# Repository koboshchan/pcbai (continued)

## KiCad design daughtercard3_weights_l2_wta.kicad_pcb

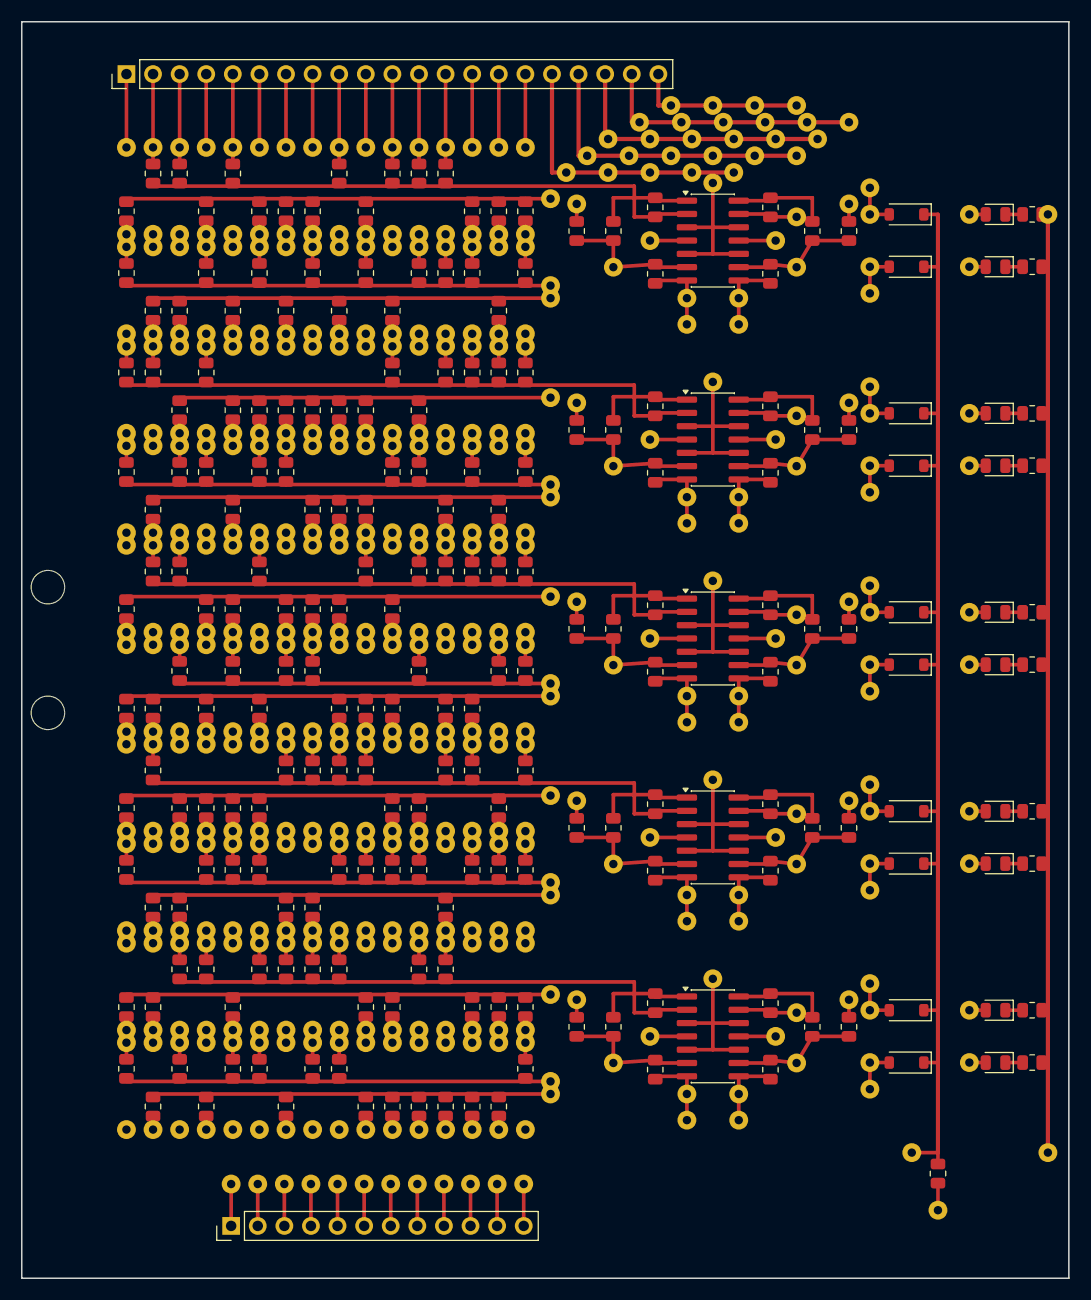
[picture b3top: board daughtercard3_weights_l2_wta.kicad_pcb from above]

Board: 2 copper layers, 100.0 x 120.0 mm, 474 parts (0 on the bottom side), 72 nets.

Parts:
D_0, D_1, D_2, D_3, D_4, D_5, D_6, D_7, D_8, D_9: 1N4148; D_SOD-123
J_BOT: SCORES_AND_WTA; PinHeader_1x12_P2.54mm_Vertical
J_TOP: ACT_IN_AND_PWR; PinHeader_1x21_P2.54mm_Vertical
LED_0, LED_1, LED_2, LED_3, LED_4, LED_5, LED_6, LED_7, LED_8, LED_9: RED; LED_0805_2012Metric
MH1, MH2: MountingHole_3.2mm_M3
R2_0_0, R2_0_6, R2_2_1, R2_3_2, R2_3_6, R2_4_6, R2_5_5, R2_6_4, R2_6_5, R2_7_1, R2_7_2, R2_7_5, R2_8_1, R2_10_1, R2_12_6, R2_12_9: 12k; R_0805_2012Metric
R2_0_1, R2_3_0, R2_3_9, R2_4_8, R2_5_1, R2_8_2, R2_9_2, R2_9_9: 18k; R_0805_2012Metric
R2_0_2, R2_0_4, R2_2_0, R2_2_7, R2_4_3, R2_5_9, R2_6_1, R2_6_9, R2_7_3, R2_8_9, R2_9_3, R2_10_9, R2_12_3, R2_14_1, R2_14_4, R2_14_6, R2_14_7: 22k; R_0805_2012Metric
R2_0_3, R2_0_7, R2_0_8, R2_1_5, R2_2_2, R2_4_4, R2_7_4, R2_8_5, R2_9_0, R2_9_6, R2_9_7, R2_10_2, R2_10_3, R2_10_7, R2_13_4: 33k; R_0805_2012Metric
R2_0_5, R2_4_5, R2_9_1, R2_14_8: 10k; R_0805_2012Metric
R2_0_9, R2_1_0, R2_1_6, R2_1_8, R2_5_3, R2_6_2, R2_8_6, R2_8_7, R2_9_5, R2_10_5, R2_10_8, R2_11_2, R2_11_7, R2_11_9, R2_13_5, R2_13_6, R2_13_7, R2_15_3, R2_15_7, R2_15_8: 75k; R_0805_2012Metric
R2_1_1, R2_1_3, R2_1_9, R2_2_3, R2_2_5, R2_3_8, R2_4_1, R2_4_2, R2_6_6, R2_7_6, R2_7_7, R2_11_4, R2_12_4, R2_14_5, R2_15_4: 51k; R_0805_2012Metric
R2_1_2, R2_1_7, R2_11_1, R2_12_1, R2_12_8, R2_15_2, R2_15_9: 300k; R_0805_2012Metric
R2_1_4, R2_2_8, R2_4_9, R2_6_8, R2_7_8, R2_7_9, R2_8_0, R2_10_6, R2_11_0, R2_11_5, R2_11_6, R2_11_8, R2_13_1, R2_13_8, R2_15_0, R2_15_6: 100k; R_0805_2012Metric
R2_2_4, R2_12_2: 47k; R_0805_2012Metric
R2_2_6, R2_3_4, R2_4_7, R2_6_3, R2_6_7, R2_8_8, R2_9_4, R2_10_0, R2_14_2: 15k; R_0805_2012Metric
R2_2_9, R2_3_3, R2_3_5, R2_5_2, R2_7_0, R2_9_8, R2_13_2: 43k; R_0805_2012Metric
R2_3_1, R2_3_7: 390k; R_0805_2012Metric
R2_4_0, R2_5_7, R2_8_4, R2_11_3, R2_12_5, R2_13_3, R2_13_9, R2_14_0, R2_14_3, R2_14_9, R2_15_1: 200k; R_0805_2012Metric
R2_5_0, R2_5_6, R2_10_4: 7.5k; R_0805_2012Metric
R2_5_4, R2_6_0, R2_8_3: 20k; R_0805_2012Metric
R2_5_8: 470k; R_0805_2012Metric
R2_12_0, R2_15_5: 1M; R_0805_2012Metric
R2_12_7: 5.6k; R_0805_2012Metric
R2_13_0: 680k; R_0805_2012Metric
R_LED0, R_LED1, R_LED2, R_LED3, R_LED4, R_LED5, R_LED6, R_LED7, R_LED8, R_LED9: 1k; R_0805_2012Metric
R_WTA: 10k; R_0805_2012Metric
Rb_L2_0: 390k; R_0805_2012Metric
Rb_L2_1: 47k; R_0805_2012Metric
Rb_L2_2, Rb_L2_8: 200k; R_0805_2012Metric
Rb_L2_3, Rb_L2_4, Rb_L2_6, Rb_L2_7, Rb_L2_9: 100k; R_0805_2012Metric
Rb_L2_5: 1M; R_0805_2012Metric
Rc_L2_0, Rc_L2_1, Rc_L2_2, Rc_L2_3, Rc_L2_4, Rc_L2_5, Rc_L2_6, Rc_L2_7, Rc_L2_8, Rc_L2_9: 10k; R_0805_2012Metric
Rf1_L2_0, Rf1_L2_1, Rf1_L2_2, Rf1_L2_3, Rf1_L2_4, Rf1_L2_5, Rf1_L2_6, Rf1_L2_7, Rf1_L2_8, Rf1_L2_9: 10k; R_0805_2012Metric
Rf_L2_0, Rf_L2_1, Rf_L2_2, Rf_L2_3, Rf_L2_4, Rf_L2_5, Rf_L2_6, Rf_L2_7, Rf_L2_8, Rf_L2_9: 10k; R_0805_2012Metric
U1, U2, U3, U4, U5: TL074; SOIC-14_3.9x8.7mm_P1.27mm
W1, W2, W3, W4, W5, W6, W7, W8, W9, W10, W11, W12, W13, W14, W15, W16, W17, W18, W19, W20, W21, W22, W23, W24, W25, W26, W27, W28, W29, W30, W31, W32, W33, W34, W35, W36, W37, W38, W39, W40, W41, W42, W43, W44, W45, W46, W47, W48, W49, W50, W51, W52, W53, W54, W55, W56, W57, W58, W59, W60, W61, W62, W63, W64, W65, W66, W67, W68, W69, W70, W71, W72, W73, W74, W75, W76, W77, W78, W79, W80, W81, W82, W83, W84, W85, W86, W87, W88, W89, W90, W91, W92, W93, W94, W95, W96, W97, W98, W99, W100, W101, W102, W103, W104, W105, W106, W107, W108, W109, W110, W111, W112, W113, W114, W115, W116, W117, W118, W119, W120, W121, W122, W123, W124, W125, W126, W127, W128, W129, W130, W131, W132, W133, W134, W135, W136, W137, W138, W139, W140, W141, W142, W143, W144, W145, W146, W147, W148, W149, W150, W151, W152, W153, W154, W155, W156, W157, W158, W159, W160, W161, W162, W163, W164, W165, W166, W167, W168, W169, W170, W171, W172, W173, W174, W175, W176, W177, W178, W179, W180, W181, W182, W183, W184, W185, W186, W187, W188, W189, W190, W191, W192, W193, W194, W195, W196, W197, W198, W199, W200, W201, W202, W203, W204, W205, W206, W207, W208, W209, W210, W211, W212, W213, W214, W215, W216, W217, W218, W219, W220, W221, W222, W223, W224, W225, W226, W227, W228, W229, W230, W231, W232, W233, W234: JUMPER; Jumper_Wire

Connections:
+5V_REF: J_TOP.20, Rb_L2_0.1, Rb_L2_2.1, Rb_L2_3.1, Rb_L2_5.1, Rb_L2_8.1, Rb_L2_9.1, W169.1, W183.1, W186.1, W200.1, W225.1, W228.1
+12V: J_TOP.17, U1.4, U2.4, U3.4, U4.4, U5.4, W166.1, W180.1, W194.1, W208.1, W222.1
-5V_REF: J_TOP.21, Rb_L2_1.1, Rb_L2_4.1, Rb_L2_6.1, Rb_L2_7.1, W172.1, W197.1, W211.1, W214.1
-12V: J_TOP.18, R_WTA.2, U1.11, U2.11, U3.11, U4.11, U5.11, W162.1, W167.1, W181.1, W195.1, W209.1, W223.1
ACT_0: J_TOP.1, R2_0_0.1, R2_0_1.1, R2_0_2.1, R2_0_3.1, R2_0_4.1, R2_0_5.1, R2_0_6.1, R2_0_7.1, R2_0_8.1, R2_0_9.1, W1.1, W2.1, W3.1, W4.1, W5.1, W6.1, W7.1, W8.1, W9.1, W10.1
ACT_1: J_TOP.2, R2_1_0.1, R2_1_1.1, R2_1_2.1, R2_1_3.1, R2_1_4.1, R2_1_5.1, R2_1_6.1, R2_1_7.1, R2_1_8.1, R2_1_9.1, W11.1, W12.1, W13.1, W14.1, W15.1, W16.1, W17.1, W18.1, W19.1, W20.1
ACT_2: J_TOP.3, R2_2_0.1, R2_2_1.1, R2_2_2.1, R2_2_3.1, R2_2_4.1, R2_2_5.1, R2_2_6.1, R2_2_7.1, R2_2_8.1, R2_2_9.1, W21.1, W22.1, W23.1, W24.1, W25.1, W26.1, W27.1, W28.1, W29.1, W30.1
ACT_3: J_TOP.4, R2_3_0.1, R2_3_1.1, R2_3_2.1, R2_3_3.1, R2_3_4.1, R2_3_5.1, R2_3_6.1, R2_3_7.1, R2_3_8.1, R2_3_9.1, W31.1, W32.1, W33.1, W34.1, W35.1, W36.1, W37.1, W38.1, W39.1, W40.1
ACT_4: J_TOP.5, R2_4_0.1, R2_4_1.1, R2_4_2.1, R2_4_3.1, R2_4_4.1, R2_4_5.1, R2_4_6.1, R2_4_7.1, R2_4_8.1, R2_4_9.1, W41.1, W42.1, W43.1, W44.1, W45.1, W46.1, W47.1, W48.1, W49.1, W50.1
ACT_5: J_TOP.6, R2_5_0.1, R2_5_1.1, R2_5_2.1, R2_5_3.1, R2_5_4.1, R2_5_5.1, R2_5_6.1, R2_5_7.1, R2_5_8.1, R2_5_9.1, W51.1, W52.1, W53.1, W54.1, W55.1, W56.1, W57.1, W58.1, W59.1, W60.1
ACT_6: J_TOP.7, R2_6_0.1, R2_6_1.1, R2_6_2.1, R2_6_3.1, R2_6_4.1, R2_6_5.1, R2_6_6.1, R2_6_7.1, R2_6_8.1, R2_6_9.1, W61.1, W62.1, W63.1, W64.1, W65.1, W66.1, W67.1, W68.1, W69.1, W70.1
ACT_7: J_TOP.8, R2_7_0.1, R2_7_1.1, R2_7_2.1, R2_7_3.1, R2_7_4.1, R2_7_5.1, R2_7_6.1, R2_7_7.1, R2_7_8.1, R2_7_9.1, W71.1, W72.1, W73.1, W74.1, W75.1, W76.1, W77.1, W78.1, W79.1, W80.1
ACT_8: J_TOP.9, R2_8_0.1, R2_8_1.1, R2_8_2.1, R2_8_3.1, R2_8_4.1, R2_8_5.1, R2_8_6.1, R2_8_7.1, R2_8_8.1, R2_8_9.1, W81.1, W82.1, W83.1, W84.1, W85.1, W86.1, W87.1, W88.1, W89.1, W90.1
ACT_9: J_TOP.10, R2_9_0.1, R2_9_1.1, R2_9_2.1, R2_9_3.1, R2_9_4.1, R2_9_5.1, R2_9_6.1, R2_9_7.1, R2_9_8.1, R2_9_9.1, W91.1, W92.1, W93.1, W94.1, W95.1, W96.1, W97.1, W98.1, W99.1, W100.1
ACT_10: J_TOP.11, R2_10_0.1, R2_10_1.1, R2_10_2.1, R2_10_3.1, R2_10_4.1, R2_10_5.1, R2_10_6.1, R2_10_7.1, R2_10_8.1, R2_10_9.1, W101.1, W102.1, W103.1, W104.1, W105.1, W106.1, W107.1, W108.1, W109.1, W110.1
ACT_11: J_TOP.12, R2_11_0.1, R2_11_1.1, R2_11_2.1, R2_11_3.1, R2_11_4.1, R2_11_5.1, R2_11_6.1, R2_11_7.1, R2_11_8.1, R2_11_9.1, W111.1, W112.1, W113.1, W114.1, W115.1, W116.1, W117.1, W118.1, W119.1, W120.1
ACT_12: J_TOP.13, R2_12_0.1, R2_12_1.1, R2_12_2.1, R2_12_3.1, R2_12_4.1, R2_12_5.1, R2_12_6.1, R2_12_7.1, R2_12_8.1, R2_12_9.1, W121.1, W122.1, W123.1, W124.1, W125.1, W126.1, W127.1, W128.1, W129.1, W130.1
ACT_13: J_TOP.14, R2_13_0.1, R2_13_1.1, R2_13_2.1, R2_13_3.1, R2_13_4.1, R2_13_5.1, R2_13_6.1, R2_13_7.1, R2_13_8.1, R2_13_9.1, W131.1, W132.1, W133.1, W134.1, W135.1, W136.1, W137.1, W138.1, W139.1, W140.1
ACT_14: J_TOP.15, R2_14_0.1, R2_14_1.1, R2_14_2.1, R2_14_3.1, R2_14_4.1, R2_14_5.1, R2_14_6.1, R2_14_7.1, R2_14_8.1, R2_14_9.1, W141.1, W142.1, W143.1, W144.1, W145.1, W146.1, W147.1, W148.1, W149.1, W150.1
ACT_15: J_TOP.16, R2_15_0.1, R2_15_1.1, R2_15_2.1, R2_15_3.1, R2_15_4.1, R2_15_5.1, R2_15_6.1, R2_15_7.1, R2_15_8.1, R2_15_9.1, W151.1, W152.1, W153.1, W154.1, W155.1, W156.1, W157.1, W158.1, W159.1, W160.1
GND: J_BOT.12, J_TOP.19, R_LED0.2, R_LED1.2, R_LED2.2, R_LED3.2, R_LED4.2, R_LED5.2, R_LED6.2, R_LED7.2, R_LED8.2, R_LED9.2, U1.3, U1.5, U1.10, U1.12, U2.3, U2.5, U2.10, U2.12, U3.3, U3.5, U3.10, U3.12, U4.3, U4.5, U4.10, U4.12, U5.3, U5.5, U5.10, U5.12, W163.1, W164.1, W165.1, W179.1, W193.1, W207.1, W221.1
LED_NET_0: LED_0.1, R_LED0.1
LED_NET_1: LED_1.1, R_LED1.1
LED_NET_2: LED_2.1, R_LED2.1
LED_NET_3: LED_3.1, R_LED3.1
LED_NET_4: LED_4.1, R_LED4.1
LED_NET_5: LED_5.1, R_LED5.1
LED_NET_6: LED_6.1, R_LED6.1
LED_NET_7: LED_7.1, R_LED7.1
LED_NET_8: LED_8.1, R_LED8.1
LED_NET_9: LED_9.1, R_LED9.1
SUM_L2_NEG_0: R2_0_0.2, R2_3_0.2, R2_5_0.2, R2_6_0.2, R2_7_0.2, R2_9_0.2, R2_13_0.2, R2_14_0.2, R2_15_0.2, Rb_L2_0.2, Rc_L2_0.2, Rf_L2_0.1, U1.6, W168.1
SUM_L2_NEG_1: R2_1_1.2, R2_2_1.2, R2_4_1.2, R2_6_1.2, R2_8_1.2, R2_10_1.2, R2_14_1.2, Rb_L2_1.2, Rc_L2_1.2, Rf_L2_1.1, U1.9, W171.1
SUM_L2_NEG_2: R2_2_2.2, R2_4_2.2, R2_5_2.2, R2_6_2.2, R2_7_2.2, R2_8_2.2, R2_9_2.2, R2_11_2.2, Rb_L2_2.2, Rc_L2_2.2, Rf_L2_2.1, U2.6, W182.1
SUM_L2_NEG_3: R2_1_3.2, R2_4_3.2, R2_7_3.2, R2_8_3.2, R2_9_3.2, R2_12_3.2, R2_14_3.2, Rb_L2_3.2, Rc_L2_3.2, Rf_L2_3.1, U2.9, W185.1
SUM_L2_NEG_4: R2_0_4.2, R2_3_4.2, R2_4_4.2, R2_6_4.2, R2_7_4.2, R2_8_4.2, R2_10_4.2, Rb_L2_4.2, Rc_L2_4.2, Rf_L2_4.1, U3.6, W196.1
SUM_L2_NEG_5: R2_0_5.2, R2_1_5.2, R2_3_5.2, R2_5_5.2, R2_8_5.2, R2_9_5.2, R2_10_5.2, R2_12_5.2, R2_13_5.2, Rb_L2_5.2, Rc_L2_5.2, Rf_L2_5.1, U3.9, W199.1
SUM_L2_NEG_6: R2_0_6.2, R2_2_6.2, R2_3_6.2, R2_4_6.2, R2_5_6.2, R2_10_6.2, R2_11_6.2, R2_14_6.2, Rb_L2_6.2, Rc_L2_6.2, Rf_L2_6.1, U4.6, W210.1
SUM_L2_NEG_7: R2_1_7.2, R2_2_7.2, R2_6_7.2, R2_7_7.2, R2_12_7.2, Rb_L2_7.2, Rc_L2_7.2, Rf_L2_7.1, U4.9, W213.1
SUM_L2_NEG_8: R2_0_8.2, R2_1_8.2, R2_4_8.2, R2_9_8.2, R2_10_8.2, R2_13_8.2, R2_14_8.2, R2_15_8.2, Rb_L2_8.2, Rc_L2_8.2, Rf_L2_8.1, U5.6, W224.1
SUM_L2_NEG_9: R2_1_9.2, R2_3_9.2, R2_6_9.2, R2_9_9.2, R2_10_9.2, R2_11_9.2, R2_12_9.2, R2_13_9.2, R2_14_9.2, Rb_L2_9.2, Rc_L2_9.2, Rf_L2_9.1, U5.9, W227.1
SUM_L2_POS_0: R2_1_0.2, R2_2_0.2, R2_4_0.2, R2_8_0.2, R2_10_0.2, R2_11_0.2, R2_12_0.2, Rf1_L2_0.2, U1.2
SUM_L2_POS_1: R2_0_1.2, R2_3_1.2, R2_5_1.2, R2_7_1.2, R2_9_1.2, R2_11_1.2, R2_12_1.2, R2_13_1.2, R2_15_1.2, Rf1_L2_1.2, U1.13, W170.1
SUM_L2_POS_2: R2_0_2.2, R2_1_2.2, R2_3_2.2, R2_10_2.2, R2_12_2.2, R2_13_2.2, R2_14_2.2, R2_15_2.2, Rf1_L2_2.2, U2.2
SUM_L2_POS_3: R2_0_3.2, R2_2_3.2, R2_3_3.2, R2_5_3.2, R2_6_3.2, R2_10_3.2, R2_11_3.2, R2_13_3.2, R2_15_3.2, Rf1_L2_3.2, U2.13, W184.1
SUM_L2_POS_4: R2_1_4.2, R2_2_4.2, R2_5_4.2, R2_9_4.2, R2_11_4.2, R2_12_4.2, R2_13_4.2, R2_14_4.2, R2_15_4.2, Rf1_L2_4.2, U3.2
SUM_L2_POS_5: R2_2_5.2, R2_4_5.2, R2_6_5.2, R2_7_5.2, R2_11_5.2, R2_14_5.2, R2_15_5.2, Rf1_L2_5.2, U3.13, W198.1
SUM_L2_POS_6: R2_1_6.2, R2_6_6.2, R2_7_6.2, R2_8_6.2, R2_9_6.2, R2_12_6.2, R2_13_6.2, R2_15_6.2, Rf1_L2_6.2, U4.2
SUM_L2_POS_7: R2_0_7.2, R2_3_7.2, R2_4_7.2, R2_5_7.2, R2_8_7.2, R2_9_7.2, R2_10_7.2, R2_11_7.2, R2_13_7.2, R2_14_7.2, R2_15_7.2, Rf1_L2_7.2, U4.13, W212.1
SUM_L2_POS_8: R2_2_8.2, R2_3_8.2, R2_5_8.2, R2_6_8.2, R2_7_8.2, R2_8_8.2, R2_11_8.2, R2_12_8.2, Rf1_L2_8.2, U5.2
SUM_L2_POS_9: R2_0_9.2, R2_2_9.2, R2_4_9.2, R2_5_9.2, R2_7_9.2, R2_8_9.2, R2_15_9.2, Rf1_L2_9.2, U5.13, W226.1
V_INV_0: Rc_L2_0.1, Rf1_L2_0.1, U1.1
V_INV_1: Rc_L2_1.1, Rf1_L2_1.1, U1.14
V_INV_2: Rc_L2_2.1, Rf1_L2_2.1, U2.1
V_INV_3: Rc_L2_3.1, Rf1_L2_3.1, U2.14
V_INV_4: Rc_L2_4.1, Rf1_L2_4.1, U3.1
V_INV_5: Rc_L2_5.1, Rf1_L2_5.1, U3.14
V_INV_6: Rc_L2_6.1, Rf1_L2_6.1, U4.1
V_INV_7: Rc_L2_7.1, Rf1_L2_7.1, U4.14
V_INV_8: Rc_L2_8.1, Rf1_L2_8.1, U5.1
V_INV_9: Rc_L2_9.1, Rf1_L2_9.1, U5.14
V_SUM_0: D_0.2, J_BOT.1, LED_0.2, Rf_L2_0.2, U1.7, W173.1, W174.1, W175.1
V_SUM_1: D_1.2, J_BOT.2, LED_1.2, Rf_L2_1.2, U1.8, W176.1, W177.1, W178.1
V_SUM_2: D_2.2, J_BOT.3, LED_2.2, Rf_L2_2.2, U2.7, W187.1, W188.1, W189.1
V_SUM_3: D_3.2, J_BOT.4, LED_3.2, Rf_L2_3.2, U2.8, W190.1, W191.1, W192.1
V_SUM_4: D_4.2, J_BOT.5, LED_4.2, Rf_L2_4.2, U3.7, W201.1, W202.1, W203.1
V_SUM_5: D_5.2, J_BOT.6, LED_5.2, Rf_L2_5.2, U3.8, W204.1, W205.1, W206.1
V_SUM_6: D_6.2, J_BOT.7, LED_6.2, Rf_L2_6.2, U4.7, W215.1, W216.1, W217.1
V_SUM_7: D_7.2, J_BOT.8, LED_7.2, Rf_L2_7.2, U4.8, W218.1, W219.1, W220.1
V_SUM_8: D_8.2, J_BOT.9, LED_8.2, Rf_L2_8.2, U5.7, W229.1, W230.1, W231.1
V_SUM_9: D_9.2, J_BOT.10, LED_9.2, Rf_L2_9.2, U5.8, W232.1, W233.1, W234.1
WTA_BUS: D_0.1, D_1.1, D_2.1, D_3.1, D_4.1, D_5.1, D_6.1, D_7.1, D_8.1, D_9.1, J_BOT.11, R_WTA.1, W161.1

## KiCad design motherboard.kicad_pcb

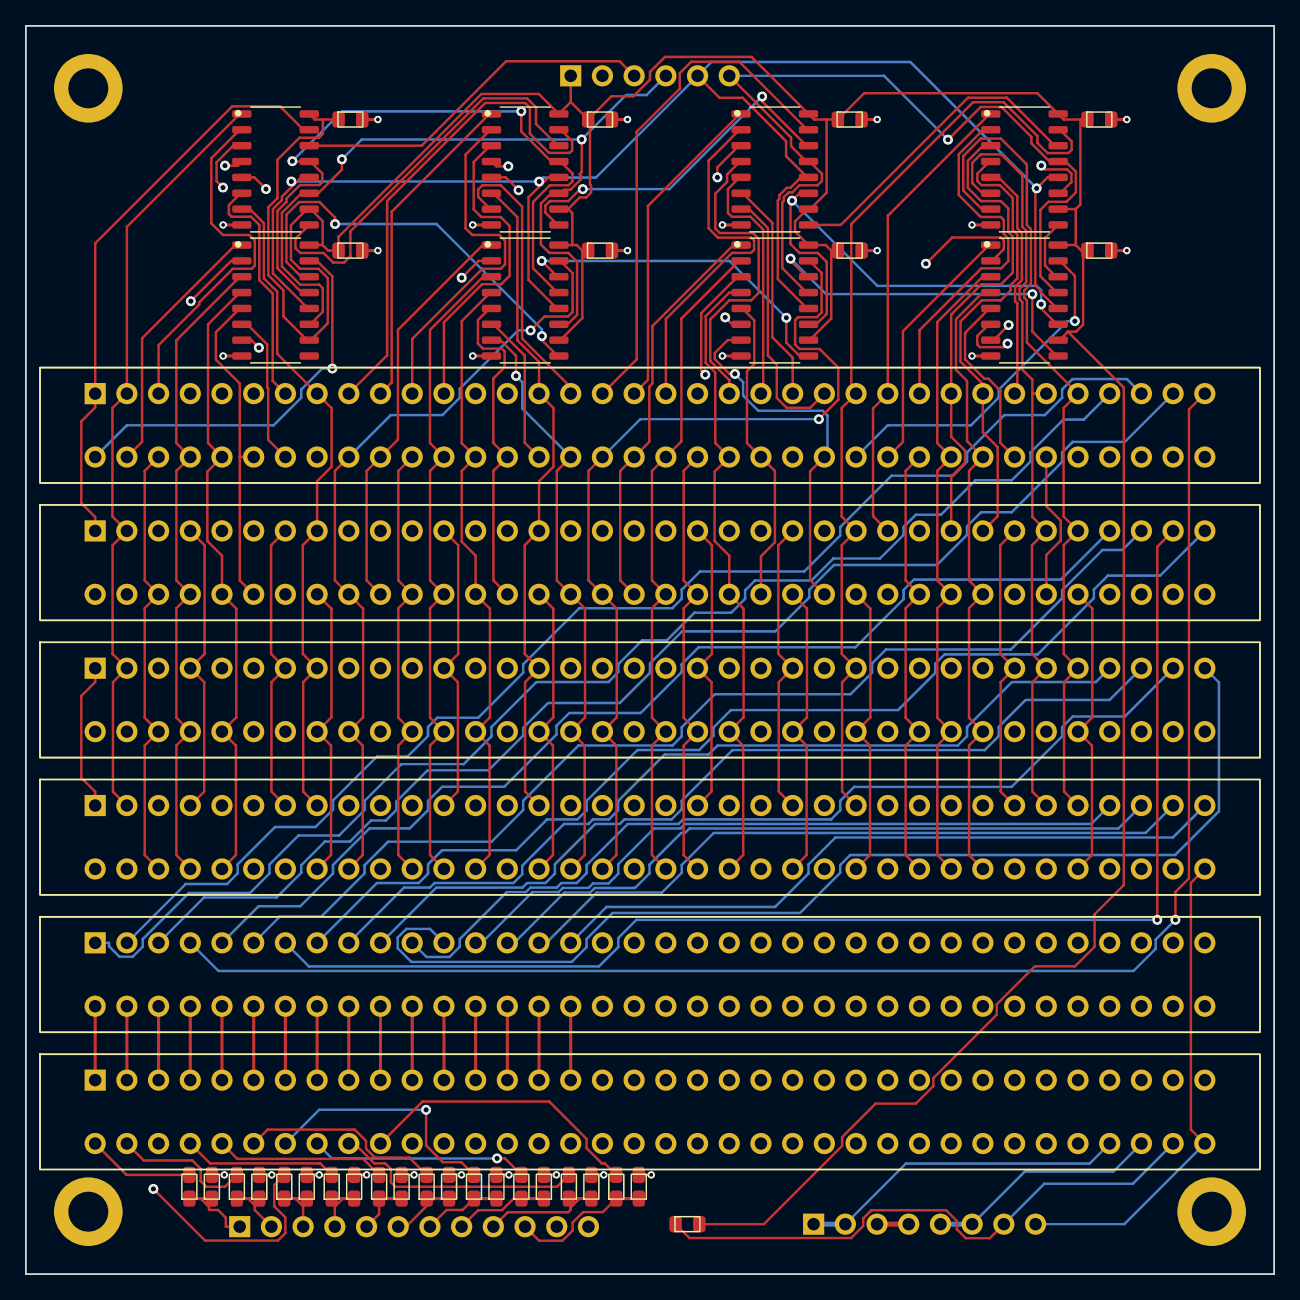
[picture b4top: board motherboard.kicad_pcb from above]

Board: 4 copper layers, 100.0 x 100.0 mm, 50 parts (0 on the bottom side), 133 nets.

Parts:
C_SR1, C_SR2, C_SR3, C_SR4, C_SR5, C_SR6, C_SR7, C_SR8: 0.1uF; C_0805_2012Metric
H1, H2, H3, H4: MountingHole; MountingHole_3.2mm_M3_Pad
J_MCU_SCORES: Scores_DIV_3V3_Out; PinHeader_1x12_P2.54mm_Vertical
J_MCU_SPI: MCU_SPI_In; PinHeader_1x06_P2.54mm_Vertical
J_PWR_IN: Main_Power_In; PinHeader_1x08_P2.54mm_Vertical
J_SLOT0: Slot0: DC1A (L1 Neurons 0..3); S-072M-2.54-5
J_SLOT1: Slot1: DC1B (L1 Neurons 4..7); S-072M-2.54-5
J_SLOT2: Slot2: DC1C (L1 Neurons 8..11); S-072M-2.54-5
J_SLOT3: Slot3: DC1D (L1 Neurons 12..15); S-072M-2.54-5
J_SLOT4: Slot4: DC2 (16x Active Precision ReLU); S-072M-2.54-5
J_SLOT5: Slot5: DC3 (L2 Weights + 10-Way WTA); S-072M-2.54-5
R_BOT_0, R_BOT_1, R_BOT_2, R_BOT_3, R_BOT_4, R_BOT_5, R_BOT_6, R_BOT_7, R_BOT_8, R_BOT_9: 20k; R_0805_2012Metric
R_PWR5: 0R; R_0805_2012Metric
R_TOP_0, R_TOP_1, R_TOP_2, R_TOP_3, R_TOP_4, R_TOP_5, R_TOP_6, R_TOP_7, R_TOP_8, R_TOP_9: 10k; R_0805_2012Metric
U_SR1, U_SR2, U_SR3, U_SR4, U_SR5, U_SR6, U_SR7, U_SR8: 74HC595D; SOIC-16_3.9x9.9mm_P1.27mm

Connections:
+5V: C_SR1.1, C_SR2.1, C_SR3.1, C_SR4.1, C_SR5.1, C_SR6.1, C_SR7.1, C_SR8.1, J_MCU_SPI.1, R_PWR5.2, U_SR1.10, U_SR1.16, U_SR2.10, U_SR2.16, U_SR3.10, U_SR3.16, U_SR4.10, U_SR4.16, U_SR5.10, U_SR5.16, U_SR6.10, U_SR6.16, U_SR7.10, U_SR7.16, U_SR8.10, U_SR8.16
+5V_REF: J_PWR_IN.7, J_SLOT0.B35, J_SLOT1.B35, J_SLOT2.B35, J_SLOT3.B35, J_SLOT5.B35, R_PWR5.1
+12V: J_PWR_IN.1, J_PWR_IN.2, J_SLOT0.B33, J_SLOT1.B33, J_SLOT2.B33, J_SLOT3.B33, J_SLOT4.B33, J_SLOT5.B33
-5V_REF: J_PWR_IN.8, J_SLOT0.B36, J_SLOT1.B36, J_SLOT2.B36, J_SLOT3.B36, J_SLOT5.B36
-12V: J_PWR_IN.5, J_PWR_IN.6, J_SLOT0.B34, J_SLOT1.B34, J_SLOT2.B34, J_SLOT3.B34, J_SLOT4.B34, J_SLOT5.B34
ACT_0: J_SLOT4.B1, J_SLOT5.A1
ACT_1: J_SLOT4.B2, J_SLOT5.A2
ACT_2: J_SLOT4.B3, J_SLOT5.A3
ACT_3: J_SLOT4.B4, J_SLOT5.A4
ACT_4: J_SLOT4.B5, J_SLOT5.A5
ACT_5: J_SLOT4.B6, J_SLOT5.A6
ACT_6: J_SLOT4.B7, J_SLOT5.A7
ACT_7: J_SLOT4.B8, J_SLOT5.A8
ACT_8: J_SLOT4.B9, J_SLOT5.A9
ACT_9: J_SLOT4.B10, J_SLOT5.A10
ACT_10: J_SLOT4.B11, J_SLOT5.A11
ACT_11: J_SLOT4.B12, J_SLOT5.A12
ACT_12: J_SLOT4.B13, J_SLOT5.A13
ACT_13: J_SLOT4.B14, J_SLOT5.A14
ACT_14: J_SLOT4.B15, J_SLOT5.A15
ACT_15: J_SLOT4.B16, J_SLOT5.A16
GND: C_SR1.2, C_SR2.2, C_SR3.2, C_SR4.2, C_SR5.2, C_SR6.2, C_SR7.2, C_SR8.2, H1.1, H2.1, H3.1, H4.1, J_MCU_SCORES.11, J_MCU_SCORES.12, J_MCU_SPI.2, J_PWR_IN.3, J_PWR_IN.4, J_SLOT4.A17, J_SLOT4.A18, J_SLOT4.A19, J_SLOT4.A20, J_SLOT4.A21, J_SLOT4.A22, J_SLOT4.A23, J_SLOT4.A24, J_SLOT4.A25, J_SLOT4.A26, J_SLOT4.A27, J_SLOT4.A28, J_SLOT4.A29, J_SLOT4.A30, J_SLOT4.A31, J_SLOT4.A32, J_SLOT4.A33, J_SLOT4.A34, J_SLOT4.A35, J_SLOT4.A36, J_SLOT4.B17, J_SLOT4.B18, J_SLOT4.B19, J_SLOT4.B20, J_SLOT4.B21, J_SLOT4.B22, J_SLOT4.B23, J_SLOT4.B24, J_SLOT4.B25, J_SLOT4.B26, J_SLOT4.B27, J_SLOT4.B28, J_SLOT4.B29, J_SLOT4.B30, J_SLOT4.B31, J_SLOT4.B32, J_SLOT4.B35, J_SLOT4.B36, J_SLOT5.A17, J_SLOT5.A18, J_SLOT5.A19, J_SLOT5.A20, J_SLOT5.A21, J_SLOT5.A22, J_SLOT5.A23, J_SLOT5.A24, J_SLOT5.A25, J_SLOT5.A26, J_SLOT5.A27, J_SLOT5.A28, J_SLOT5.A29, J_SLOT5.A30, J_SLOT5.A31, J_SLOT5.A32, J_SLOT5.A33, J_SLOT5.A34, J_SLOT5.A35, J_SLOT5.A36, J_SLOT5.B11, J_SLOT5.B12, J_SLOT5.B13, J_SLOT5.B14, J_SLOT5.B15, J_SLOT5.B16, J_SLOT5.B17, J_SLOT5.B18, J_SLOT5.B19, J_SLOT5.B20, J_SLOT5.B21, J_SLOT5.B22, J_SLOT5.B23, J_SLOT5.B24, J_SLOT5.B25, J_SLOT5.B26, J_SLOT5.B27, J_SLOT5.B28, J_SLOT5.B29, J_SLOT5.B30, J_SLOT5.B31, J_SLOT5.B32, R_BOT_0.2, R_BOT_1.2, R_BOT_2.2, R_BOT_3.2, R_BOT_4.2, R_BOT_5.2, R_BOT_6.2, R_BOT_7.2, R_BOT_8.2, R_BOT_9.2, U_SR1.8, U_SR2.8, U_SR3.8, U_SR4.8, U_SR5.8, U_SR6.8, U_SR7.8, U_SR8.8
IN_0: J_SLOT0.A1, J_SLOT1.A1, J_SLOT2.A1, J_SLOT3.A1, U_SR1.15
IN_1: J_SLOT0.A2, J_SLOT1.A2, J_SLOT2.A2, J_SLOT3.A2, U_SR1.1
IN_2: J_SLOT0.A3, J_SLOT1.A3, J_SLOT2.A3, J_SLOT3.A3, U_SR1.2
IN_3: J_SLOT0.A4, J_SLOT1.A4, J_SLOT2.A4, J_SLOT3.A4, U_SR1.3
IN_4: J_SLOT0.A5, J_SLOT1.A5, J_SLOT2.A5, J_SLOT3.A5, U_SR1.4
IN_5: J_SLOT0.A6, J_SLOT1.A6, J_SLOT2.A6, J_SLOT3.A6, U_SR1.5
IN_6: J_SLOT0.A7, J_SLOT1.A7, J_SLOT2.A7, J_SLOT3.A7, U_SR1.6
IN_7: J_SLOT0.A8, J_SLOT1.A8, J_SLOT2.A8, J_SLOT3.A8, U_SR1.7
IN_8: J_SLOT0.A9, J_SLOT1.A9, J_SLOT2.A9, J_SLOT3.A9, U_SR2.15
IN_9: J_SLOT0.A10, J_SLOT1.A10, J_SLOT2.A10, J_SLOT3.A10, U_SR2.1
IN_10: J_SLOT0.A11, J_SLOT1.A11, J_SLOT2.A11, J_SLOT3.A11, U_SR2.2
IN_11: J_SLOT0.A12, J_SLOT1.A12, J_SLOT2.A12, J_SLOT3.A12, U_SR2.3
IN_12: J_SLOT0.A13, J_SLOT1.A13, J_SLOT2.A13, J_SLOT3.A13, U_SR2.4
IN_13: J_SLOT0.A14, J_SLOT1.A14, J_SLOT2.A14, J_SLOT3.A14, U_SR2.5
IN_14: J_SLOT0.A15, J_SLOT1.A15, J_SLOT2.A15, J_SLOT3.A15, U_SR2.6
IN_15: J_SLOT0.A16, J_SLOT1.A16, J_SLOT2.A16, J_SLOT3.A16, U_SR2.7
IN_16: J_SLOT0.A17, J_SLOT1.A17, J_SLOT2.A17, J_SLOT3.A17, U_SR3.15
IN_17: J_SLOT0.A18, J_SLOT1.A18, J_SLOT2.A18, J_SLOT3.A18, U_SR3.1
IN_18: J_SLOT0.A19, J_SLOT1.A19, J_SLOT2.A19, J_SLOT3.A19, U_SR3.2
IN_19: J_SLOT0.A20, J_SLOT1.A20, J_SLOT2.A20, J_SLOT3.A20, U_SR3.3
IN_20: J_SLOT0.A21, J_SLOT1.A21, J_SLOT2.A21, J_SLOT3.A21, U_SR3.4
IN_21: J_SLOT0.A22, J_SLOT1.A22, J_SLOT2.A22, J_SLOT3.A22, U_SR3.5
IN_22: J_SLOT0.A23, J_SLOT1.A23, J_SLOT2.A23, J_SLOT3.A23, U_SR3.6
IN_23: J_SLOT0.A24, J_SLOT1.A24, J_SLOT2.A24, J_SLOT3.A24, U_SR3.7
IN_24: J_SLOT0.A25, J_SLOT1.A25, J_SLOT2.A25, J_SLOT3.A25, U_SR4.15
IN_25: J_SLOT0.A26, J_SLOT1.A26, J_SLOT2.A26, J_SLOT3.A26, U_SR4.1
IN_26: J_SLOT0.A27, J_SLOT1.A27, J_SLOT2.A27, J_SLOT3.A27, U_SR4.2
IN_27: J_SLOT0.A28, J_SLOT1.A28, J_SLOT2.A28, J_SLOT3.A28, U_SR4.3
IN_28: J_SLOT0.A29, J_SLOT1.A29, J_SLOT2.A29, J_SLOT3.A29, U_SR4.4
IN_29: J_SLOT0.A30, J_SLOT1.A30, J_SLOT2.A30, J_SLOT3.A30, U_SR4.5
IN_30: J_SLOT0.A31, J_SLOT1.A31, J_SLOT2.A31, J_SLOT3.A31, U_SR4.6
IN_31: J_SLOT0.A32, J_SLOT1.A32, J_SLOT2.A32, J_SLOT3.A32, U_SR4.7
IN_32: J_SLOT0.B1, J_SLOT1.B1, J_SLOT2.B1, J_SLOT3.B1, U_SR8.15
IN_33: J_SLOT0.B2, J_SLOT1.B2, J_SLOT2.B2, J_SLOT3.B2, U_SR8.1
IN_34: J_SLOT0.B3, J_SLOT1.B3, J_SLOT2.B3, J_SLOT3.B3, U_SR8.2
IN_35: J_SLOT0.B4, J_SLOT1.B4, J_SLOT2.B4, J_SLOT3.B4, U_SR8.3
IN_36: J_SLOT0.B5, J_SLOT1.B5, J_SLOT2.B5, J_SLOT3.B5, U_SR8.4
IN_37: J_SLOT0.B6, J_SLOT1.B6, J_SLOT2.B6, J_SLOT3.B6, U_SR8.5
IN_38: J_SLOT0.B7, J_SLOT1.B7, J_SLOT2.B7, J_SLOT3.B7, U_SR8.6
IN_39: J_SLOT0.B8, J_SLOT1.B8, J_SLOT2.B8, J_SLOT3.B8, U_SR8.7
IN_40: J_SLOT0.B9, J_SLOT1.B9, J_SLOT2.B9, J_SLOT3.B9, U_SR7.15
IN_41: J_SLOT0.B10, J_SLOT1.B10, J_SLOT2.B10, J_SLOT3.B10, U_SR7.1
IN_42: J_SLOT0.B11, J_SLOT1.B11, J_SLOT2.B11, J_SLOT3.B11, U_SR7.2
IN_43: J_SLOT0.B12, J_SLOT1.B12, J_SLOT2.B12, J_SLOT3.B12, U_SR7.3
IN_44: J_SLOT0.B13, J_SLOT1.B13, J_SLOT2.B13, J_SLOT3.B13, U_SR7.4
IN_45: J_SLOT0.B14, J_SLOT1.B14, J_SLOT2.B14, J_SLOT3.B14, U_SR7.5
IN_46: J_SLOT0.B15, J_SLOT1.B15, J_SLOT2.B15, J_SLOT3.B15, U_SR7.6
IN_47: J_SLOT0.B16, J_SLOT1.B16, J_SLOT2.B16, J_SLOT3.B16, U_SR7.7
IN_48: J_SLOT0.B17, J_SLOT1.B17, J_SLOT2.B17, J_SLOT3.B17, U_SR6.15
IN_49: J_SLOT0.B18, J_SLOT1.B18, J_SLOT2.B18, J_SLOT3.B18, U_SR6.1
IN_50: J_SLOT0.B19, J_SLOT1.B19, J_SLOT2.B19, J_SLOT3.B19, U_SR6.2
IN_51: J_SLOT0.B20, J_SLOT1.B20, J_SLOT2.B20, J_SLOT3.B20, U_SR6.3
IN_52: J_SLOT0.B21, J_SLOT1.B21, J_SLOT2.B21, J_SLOT3.B21, U_SR6.4
IN_53: J_SLOT0.B22, J_SLOT1.B22, J_SLOT2.B22, J_SLOT3.B22, U_SR6.5
IN_54: J_SLOT0.B23, J_SLOT1.B23, J_SLOT2.B23, J_SLOT3.B23, U_SR6.6
IN_55: J_SLOT0.B24, J_SLOT1.B24, J_SLOT2.B24, J_SLOT3.B24, U_SR6.7
IN_56: J_SLOT0.B25, J_SLOT1.B25, J_SLOT2.B25, J_SLOT3.B25, U_SR5.15
IN_57: J_SLOT0.B26, J_SLOT1.B26, J_SLOT2.B26, J_SLOT3.B26, U_SR5.1
IN_58: J_SLOT0.B27, J_SLOT1.B27, J_SLOT2.B27, J_SLOT3.B27, U_SR5.2
IN_59: J_SLOT0.B28, J_SLOT1.B28, J_SLOT2.B28, J_SLOT3.B28, U_SR5.3
IN_60: J_SLOT0.B29, J_SLOT1.B29, J_SLOT2.B29, J_SLOT3.B29, U_SR5.4
IN_61: J_SLOT0.B30, J_SLOT1.B30, J_SLOT2.B30, J_SLOT3.B30, U_SR5.5
IN_62: J_SLOT0.B31, J_SLOT1.B31, J_SLOT2.B31, J_SLOT3.B31, U_SR5.6
IN_63: J_SLOT0.B32, J_SLOT1.B32, J_SLOT2.B32, J_SLOT3.B32, U_SR5.7
SCORE_0: J_SLOT5.B1, R_TOP_0.2
SCORE_1: J_SLOT5.B2, R_TOP_1.2
SCORE_2: J_SLOT5.B3, R_TOP_2.2
SCORE_3: J_SLOT5.B4, R_TOP_3.2
SCORE_4: J_SLOT5.B5, R_TOP_4.2
SCORE_5: J_SLOT5.B6, R_TOP_5.2
SCORE_6: J_SLOT5.B7, R_TOP_6.2
SCORE_7: J_SLOT5.B8, R_TOP_7.2
SCORE_8: J_SLOT5.B9, R_TOP_8.2
SCORE_9: J_SLOT5.B10, R_TOP_9.2
SCORE_DIV_0: J_MCU_SCORES.1, R_BOT_0.1, R_TOP_0.1
SCORE_DIV_1: J_MCU_SCORES.2, R_BOT_1.1, R_TOP_1.1
SCORE_DIV_2: J_MCU_SCORES.3, R_BOT_2.1, R_TOP_2.1
SCORE_DIV_3: J_MCU_SCORES.4, R_BOT_3.1, R_TOP_3.1
SCORE_DIV_4: J_MCU_SCORES.5, R_BOT_4.1, R_TOP_4.1
SCORE_DIV_5: J_MCU_SCORES.6, R_BOT_5.1, R_TOP_5.1
SCORE_DIV_6: J_MCU_SCORES.7, R_BOT_6.1, R_TOP_6.1
SCORE_DIV_7: J_MCU_SCORES.8, R_BOT_7.1, R_TOP_7.1
SCORE_DIV_8: J_MCU_SCORES.9, R_BOT_8.1, R_TOP_8.1
SCORE_DIV_9: J_MCU_SCORES.10, R_BOT_9.1, R_TOP_9.1
SPI_LATCH: J_MCU_SPI.5, U_SR1.12, U_SR2.12, U_SR3.12, U_SR4.12, U_SR5.12, U_SR6.12, U_SR7.12, U_SR8.12
SPI_MOSI: J_MCU_SPI.3, U_SR1.14
SPI_OE: J_MCU_SPI.6, U_SR1.13, U_SR2.13, U_SR3.13, U_SR4.13, U_SR5.13, U_SR6.13, U_SR7.13, U_SR8.13
SPI_SCK: J_MCU_SPI.4, U_SR1.11, U_SR2.11, U_SR3.11, U_SR4.11, U_SR5.11, U_SR6.11, U_SR7.11, U_SR8.11
SR_CHAIN_1: U_SR1.9, U_SR2.14
SR_CHAIN_2: U_SR2.9, U_SR3.14
SR_CHAIN_3: U_SR3.9, U_SR4.14
SR_CHAIN_4: U_SR4.9, U_SR5.14
SR_CHAIN_5: U_SR5.9, U_SR6.14
SR_CHAIN_6: U_SR6.9, U_SR7.14
SR_CHAIN_7: U_SR7.9, U_SR8.14
V_SUM_0: J_SLOT0.A33, J_SLOT4.A1
V_SUM_1: J_SLOT0.A34, J_SLOT4.A2
V_SUM_2: J_SLOT0.A35, J_SLOT4.A3
V_SUM_3: J_SLOT0.A36, J_SLOT4.A4
V_SUM_4: J_SLOT1.A33, J_SLOT4.A5
V_SUM_5: J_SLOT1.A34, J_SLOT4.A6
V_SUM_6: J_SLOT1.A35, J_SLOT4.A7
V_SUM_7: J_SLOT1.A36, J_SLOT4.A8
V_SUM_8: J_SLOT2.A33, J_SLOT4.A9
V_SUM_9: J_SLOT2.A34, J_SLOT4.A10
V_SUM_10: J_SLOT2.A35, J_SLOT4.A11
V_SUM_11: J_SLOT2.A36, J_SLOT4.A12
V_SUM_12: J_SLOT3.A33, J_SLOT4.A13
V_SUM_13: J_SLOT3.A34, J_SLOT4.A14
V_SUM_14: J_SLOT3.A35, J_SLOT4.A15
V_SUM_15: J_SLOT3.A36, J_SLOT4.A16
